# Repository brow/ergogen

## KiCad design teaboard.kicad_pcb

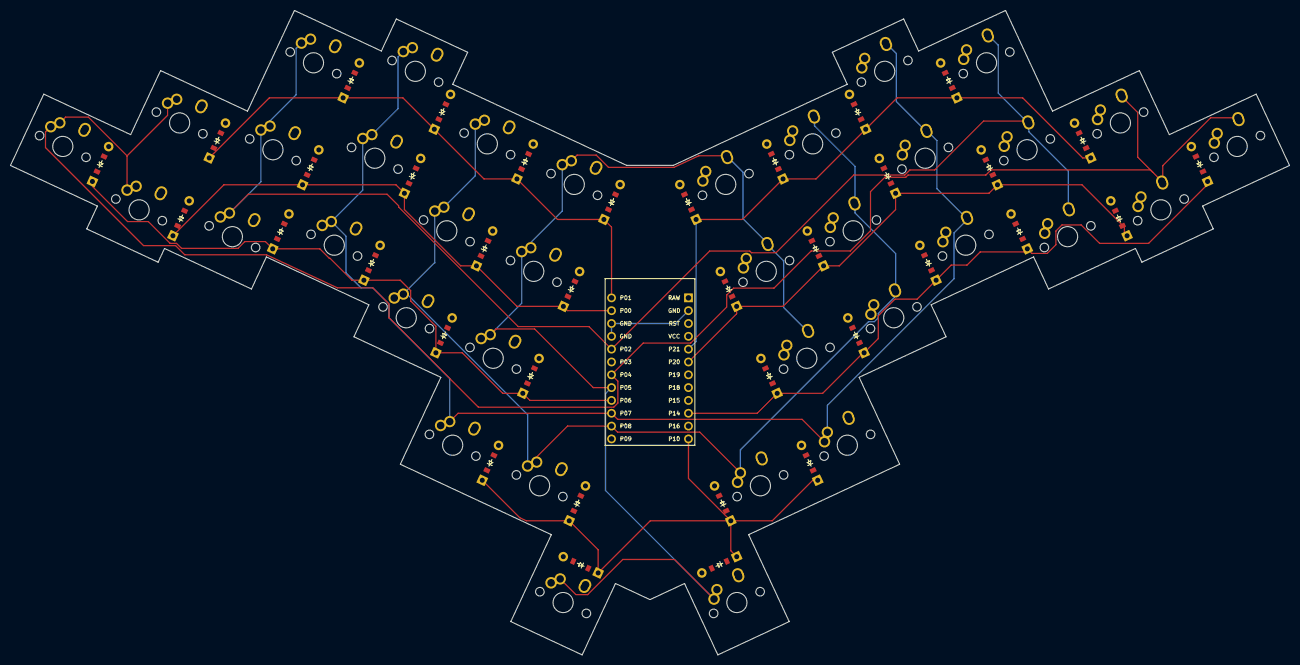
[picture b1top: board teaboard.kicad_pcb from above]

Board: 2 copper layers, 253.4 x 127.6 mm, 109 parts (0 on the bottom side), 49 nets.

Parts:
C1: ProMicro
D1, D2, D3, D4, D5, D6, D7, D8, D9, D10, D11, D12, D13, D14, D15, D16, D17, D18, D19, D20, D21, D22, D23, D24, D25, D26, D27, D28, D29, D30, D31, D32, D33, D34, D35, D36: ComboDiode
S1, S3, S5, S7, S9, S11, S13, S15, S17, S19, S21, S23, S25, S27, S29, S31, S33, S35, S37, S39, S41, S43, S45, S47, S49, S51, S53, S55, S57, S59, S61, S63, S65, S67, S69, S71: MX
S2, S4, S6, S8, S10, S12, S14, S16, S18, S20, S22, S24, S26, S28, S30, S32, S34, S36, S38, S40, S42, S44, S46, S48, S50, S52, S54, S56, S58, S60, S62, S64, S66, S68, S70, S72: ALPS

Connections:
GND: C1.2, C1.15, C1.16
P0: C1.14, D2.1, D2.2, D5.1, D5.2, D8.1, D8.2, D11.1, D11.2, D14.1, D14.2
P1: C1.13, D3.1, D3.2, D6.1, D6.2, D9.1, D9.2, D12.1, D12.2, D15.1, D15.2
P2: C1.17, S7.2, S8.2, S9.2, S10.2, S11.2, S12.2, S43.1, S44.1, S45.1, S46.1, S47.1, S48.1
P4: C1.19, S1.2, S2.2, S3.2, S4.2, S5.2, S6.2, S37.1, S38.1, S39.1, S40.1, S41.1, S42.1
P5: C1.20, S25.2, S26.2, S27.2, S28.2, S29.2, S30.2, S35.2, S36.2, S61.1, S62.1, S63.1, S64.1, S65.1, S66.1, S71.2, S72.2
P6: C1.21, D1.1, D1.2, D4.1, D4.2, D7.1, D7.2, D10.1, D10.2, D13.1, D13.2
P7: C1.22, S13.2, S14.2, S15.2, S16.2, S17.2, S18.2, S31.2, S32.2, S49.1, S50.1, S51.1, S52.1, S53.1, S54.1, S67.2, S68.2
P8: C1.23, S19.2, S20.2, S21.2, S22.2, S23.2, S24.2, S33.2, S34.2, S55.1, S56.1, S57.1, S58.1, S59.1, S60.1, S69.2, S70.2
P10: C1.12, D16.1, D16.2, D17.1, D17.2, D18.1, D18.2, D34.1, D34.2, D35.1, D35.2, D36.1, D36.2
P14: C1.10, D19.1, D19.2, D22.1, D22.2, D25.1, D25.2, D28.1, D28.2, D31.1, D31.2
P20: C1.6, D20.1, D20.2, D23.1, D23.2, D26.1, D26.2, D29.1, D29.2, D32.1, D32.2
P21: C1.5, D21.1, D21.2, D24.1, D24.2, D27.1, D27.2, D30.1, D30.2, D33.1, D33.2
far_thumb: D18.1, D18.2, S35.1, S36.1
home_thumb: D17.1, D17.2, S33.1, S34.1
index_bottom: D10.1, D10.2, S19.1, S20.1
index_home: D11.1, D11.2, S21.1, S22.1
index_top: D12.1, D12.2, S23.1, S24.1
inner_bottom: D13.1, D13.2, S25.1, S26.1
inner_home: D14.1, D14.2, S27.1, S28.1
inner_top: D15.1, D15.2, S29.1, S30.1
middle_bottom: D7.1, D7.2, S13.1, S14.1
middle_home: D8.1, D8.2, S15.1, S16.1
middle_top: D9.1, D9.2, S17.1, S18.1
mirror_far_thumb: D36.1, D36.2, S71.1, S72.1
mirror_home_thumb: D35.1, D35.2, S69.1, S70.1
mirror_index_bottom: D28.1, D28.2, S55.2, S56.2
mirror_index_home: D29.1, D29.2, S57.2, S58.2
mirror_index_top: D30.1, D30.2, S59.2, S60.2
mirror_inner_bottom: D31.1, D31.2, S61.2, S62.2
mirror_inner_home: D32.1, D32.2, S63.2, S64.2
mirror_inner_top: D33.1, D33.2, S65.2, S66.2
mirror_middle_bottom: D25.1, D25.2, S49.2, S50.2
mirror_middle_home: D26.1, D26.2, S51.2, S52.2
mirror_middle_top: D27.1, D27.2, S53.2, S54.2
mirror_near_thumb: D34.1, D34.2, S67.1, S68.1
mirror_pinky_bottom: D19.1, D19.2, S37.2, S38.2
mirror_pinky_home: D20.1, D20.2, S39.2, S40.2
mirror_pinky_top: D21.1, D21.2, S41.2, S42.2
mirror_ring_bottom: D22.1, D22.2, S43.2, S44.2
mirror_ring_home: D23.1, D23.2, S45.2, S46.2
mirror_ring_top: D24.1, D24.2, S47.2, S48.2
near_thumb: D16.1, D16.2, S31.1, S32.1
pinky_bottom: D1.1, D1.2, S1.1, S2.1
pinky_home: D2.1, D2.2, S3.1, S4.1
pinky_top: D3.1, D3.2, S5.1, S6.1
ring_bottom: D4.1, D4.2, S7.1, S8.1
ring_home: D5.1, D5.2, S9.1, S10.1
ring_top: D6.1, D6.2, S11.1, S12.1

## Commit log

2020-11-02 first stab at writing a config
2020-11-03 reduce repetition
2020-11-03 refactor using `skip`
2020-11-03 export a plate
2020-11-04 eliminate repetiton of `bind`
2020-11-04 thumb in, pinky out
2020-11-04 tweak parameters
2020-11-07 revisions from prototype
2020-11-07 MX mockup
2020-11-07 first stab at glue
2020-11-07 example of "TypeError: Cannot read property '0' of null"
2020-11-07 waypoint for glue
2020-11-08 minimal pcb
2020-11-08 refactor: no outer column
2020-11-08 use same column/row names as absolem.yaml
2020-11-08 add controller to pcb
2020-11-08 MX switch footprints
2020-11-08 add diodes
2020-11-08 add alps footprint
2020-11-10 move far thumb keys centerward
2020-11-10 remove excess PCB
2020-11-10 extra glue using a polygon
2020-11-10 shift diodes
2020-11-11 flip promicro horizontally
2020-11-12 reassign pins for easier routing
2020-11-12 remove column/row "marks"
2020-11-12 traditional grid
2020-11-12 pin assignments for easier routing
2020-11-12 move controller down
2020-11-12 tighten PCB edge
2020-11-14 Revert "pin assignments for easier routing"
    This reverts commit e34f160cf41b7729441589b2dfd700c034676773.
2020-11-14 Revert "traditional grid"
    This reverts commit c7c9f667ad73a2e7899501e7c2ba662399e03bd5.
2020-11-14 Revert "remove column/row "marks""
    This reverts commit 468be97d31e1891a35aa95644c16bc1a64491d95.
2020-11-14 Revert "reassign pins for easier routing"
    This reverts commit 4b6318c70fb68c1ada2adc1022983433a140be4a.
2020-11-14 Revert "flip promicro horizontally"
    This reverts commit 9ddf894f843d8b54ca43ea0982898202dc389129.
2020-11-14 Revert "move controller down"
    This reverts commit 923a1b6b9c3721e0136f15d73679c4955ea79d6a.
2020-11-14 refactor
2020-11-14 connector notch
2020-11-14 add choc footprint
2020-11-14 points fix
2020-11-15 cleaner notch
2020-11-15 artwork
2020-11-15 no silk labels for mcu
2020-11-16 artwork updates
2020-11-16 routing
2020-11-26 remove "marks"
2020-11-26 fix row_net for mirror-side thumbfan
2020-11-26 remove silks from promicro footprint
2021-01-01 make diode front SMD only
2021-01-01 remove silkscreen from `reset` footprint
2021-03-14 remove silkscreen from diode footprint
